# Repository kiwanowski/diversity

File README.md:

# diversity
an affordable DIY and open source alternative to the M8 tracker

## Limitations
The official firmware needs to be patched to work with this device.

## Support

[Please support the original M8 tracker author](https://www.patreon.com/trash80)

I won't provide support for any boards or schematics other than the ones provided in the repository.

I do not take reponsibility for any damage done. Please be sure that you understand what you are doing.

Creative Commons cc-by-sa 4.0 license.

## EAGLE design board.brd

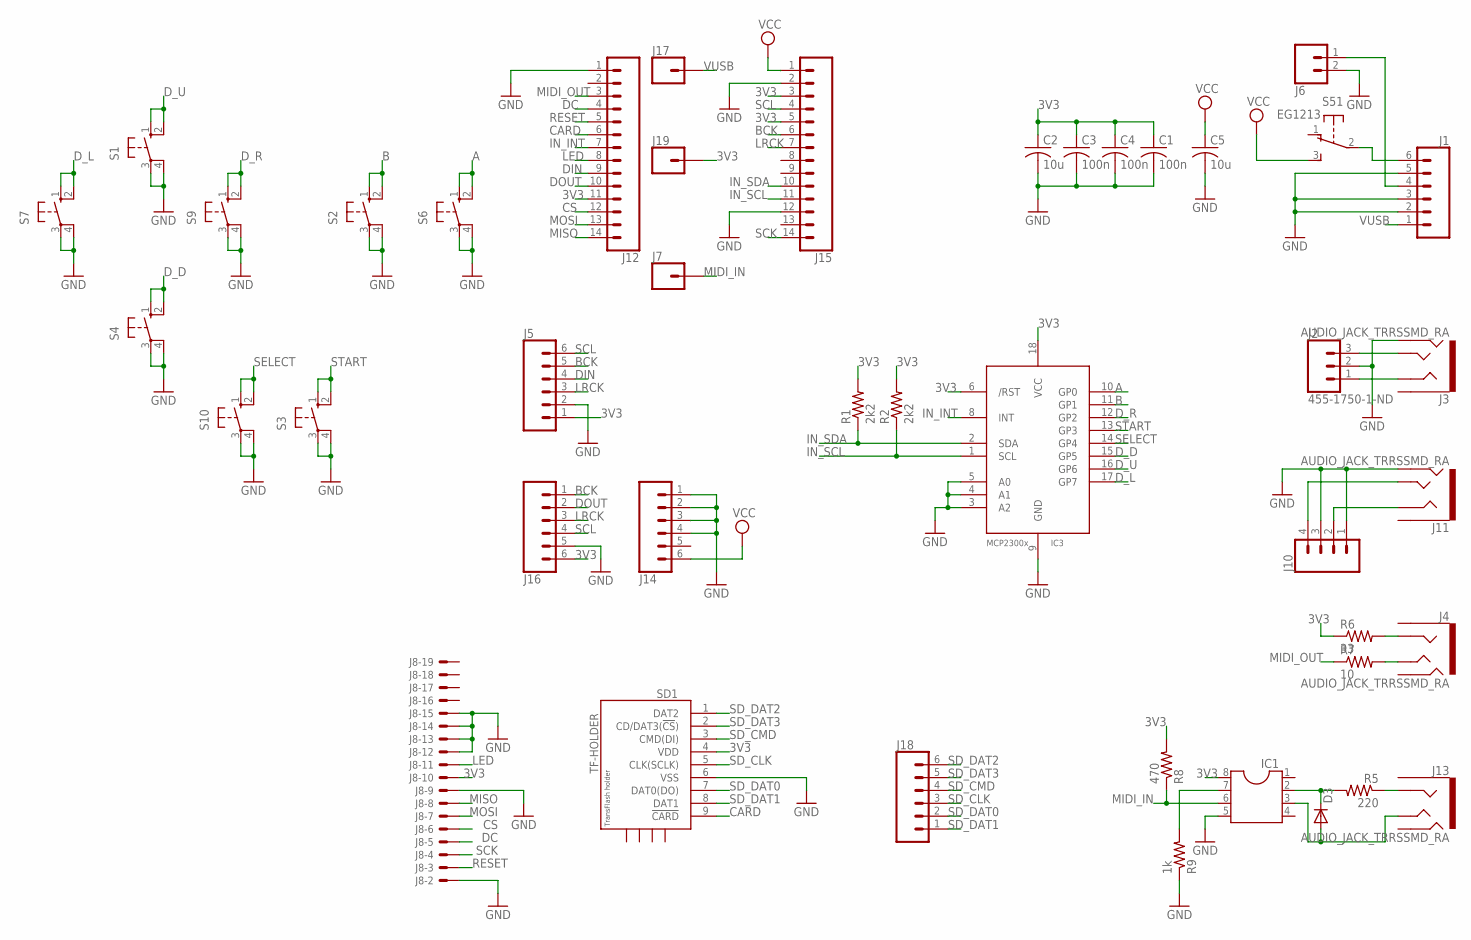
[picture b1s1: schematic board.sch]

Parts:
C1, C3, C4: 100n; C0805
C2, C5: 10u; C0805
D3: DIODE-MINIMELF; MINIMELF
IC1: DIL8; DIL08
IC3: MCP23008/SO; SO18W
J1, J5, J14, J16, J18: CONN_06SILK_FEMALE_PTH; 1X06
J2: 455-1750-1-ND; 1X03
J3, J4, J11, J13: AUDIO_JACK_TRRSSMD_RA; AUDIO_JACK_3.5MM_TRRS_SMD_RA
J6: CONN_02; 1X02
J7, J17, J19: CONN_01; 1X01
J8: XF2E-2015-1
J10: CONN_04; 1X04
J12, J15: CONN_14; 1X14
R1, R2: 2k2; R0805
R5: 220; R0805
R6: 33; R0805
R7: 10; R0805
R8: 470; R0805
R9: 1k; R0805
S1, S2, S3, S4, S6, S7, S9, S10: 10-XX; B3F-10XX
S5: EG1213
SD1: TF-HOLDER; TF-PULL

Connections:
3V3: C1.1, C2.1, C3.1, C4.1, IC1.8, IC3.6 (/RST), IC3.18 (VCC), J5.1, J8.10, J12.11, J15.3, J15.5, J16.6, J19.1, R1.2, R2.2, R6.1, R8.2, SD1.4 (VDD)
A: IC3.10 (GP0), S6.1 (S), S6.2 (S1)
B: IC3.11 (GP1), S2.1 (S), S2.2 (S1)
BCK: J5.5, J15.6, J16.1
CARD: J12.6, SD1.9 (!CARD)
CS: J8.6, J12.12
DC: J8.5, J12.4
DIN: J5.4, J12.9
DOUT: J12.10, J16.2
D_D: IC3.15 (GP5), S4.1 (S), S4.2 (S1)
D_L: IC3.17 (GP7), S7.1 (S), S7.2 (S1)
D_R: IC3.12 (GP2), S9.1 (S), S9.2 (S1)
D_U: IC3.16 (GP6), S1.1 (S), S1.2 (S1)
GND: C1.2, C2.2, C3.2, C4.2, C5.2, IC1.5, IC3.3 (A2), IC3.4 (A1), IC3.5 (A0), IC3.9 (GND), J1.2, J1.3, J1.5, J2.2, J3.RING2, J5.2, J6.2, J8.2, J8.9, J8.12, J8.13, J8.14, J8.15, J10.1, J10.3, J11.RING2, J12.1, J14.1, J14.2, J14.3, J14.4, J15.2, J15.12, J16.5, R9.1, S1.3, S1.4 (P1), S2.3, S2.4 (P1), S3.3, S3.4 (P1), S4.3, S4.4 (P1), S6.3, S6.4 (P1), S7.3, S7.4 (P1), S9.3, S9.4 (P1), S10.3, S10.4 (P1), SD1.6 (VSS)
IN_INT: IC3.8 (INT), J12.7
IN_SCL: IC3.1 (SCL), J15.11, R2.1
IN_SDA: IC3.2 (SDA), J15.10, R1.1
LED: J8.11, J12.8
LRCK: J5.3, J15.7, J16.3
MIDI_IN: IC1.6, J7.1, R8.1
MIDI_OUT: J12.3, R7.1
MISO: J8.8, J12.14
MOSI: J8.7, J12.13
unnamed: J2.3, J3.TIP
unnamed: J2.1, J3.RING1
unnamed: J10.4, J11.TIP
unnamed: J10.2, J11.RING1
unnamed: J1.4, J6.1
unnamed: J4.RING1, R6.2
unnamed: J4.TIP, R7.2
unnamed: J13.RING1, R5.1
unnamed: D3.C, IC1.2, R5.2
unnamed: D3.A, IC1.3, J13.TIP
unnamed: IC1.7, R9.2
unnamed: J1.6, S5.2
RESET: J8.3, J12.5
SCK: J8.4, J15.14
SCL: J5.6, J15.4, J16.4
SD_CLK: J18.3, SD1.5 (CLK(SCLK))
SD_CMD: J18.4, SD1.3 (CMD(DI))
SD_DAT0: J18.2, SD1.7 (DAT0(DO))
SD_DAT1: J18.1, SD1.8 (DAT1)
SD_DAT2: J18.6, SD1.1 (DAT2)
SD_DAT3: J18.5, SD1.2 (CD/DAT3(!CS!))
SELECT: IC3.14 (GP4), S10.1 (S), S10.2 (S1)
START: IC3.13 (GP3), S3.1 (S), S3.2 (S1)
VCC: C5.1, J14.6, J15.1, S5.3 (S)
VUSB: J1.1, J17.1

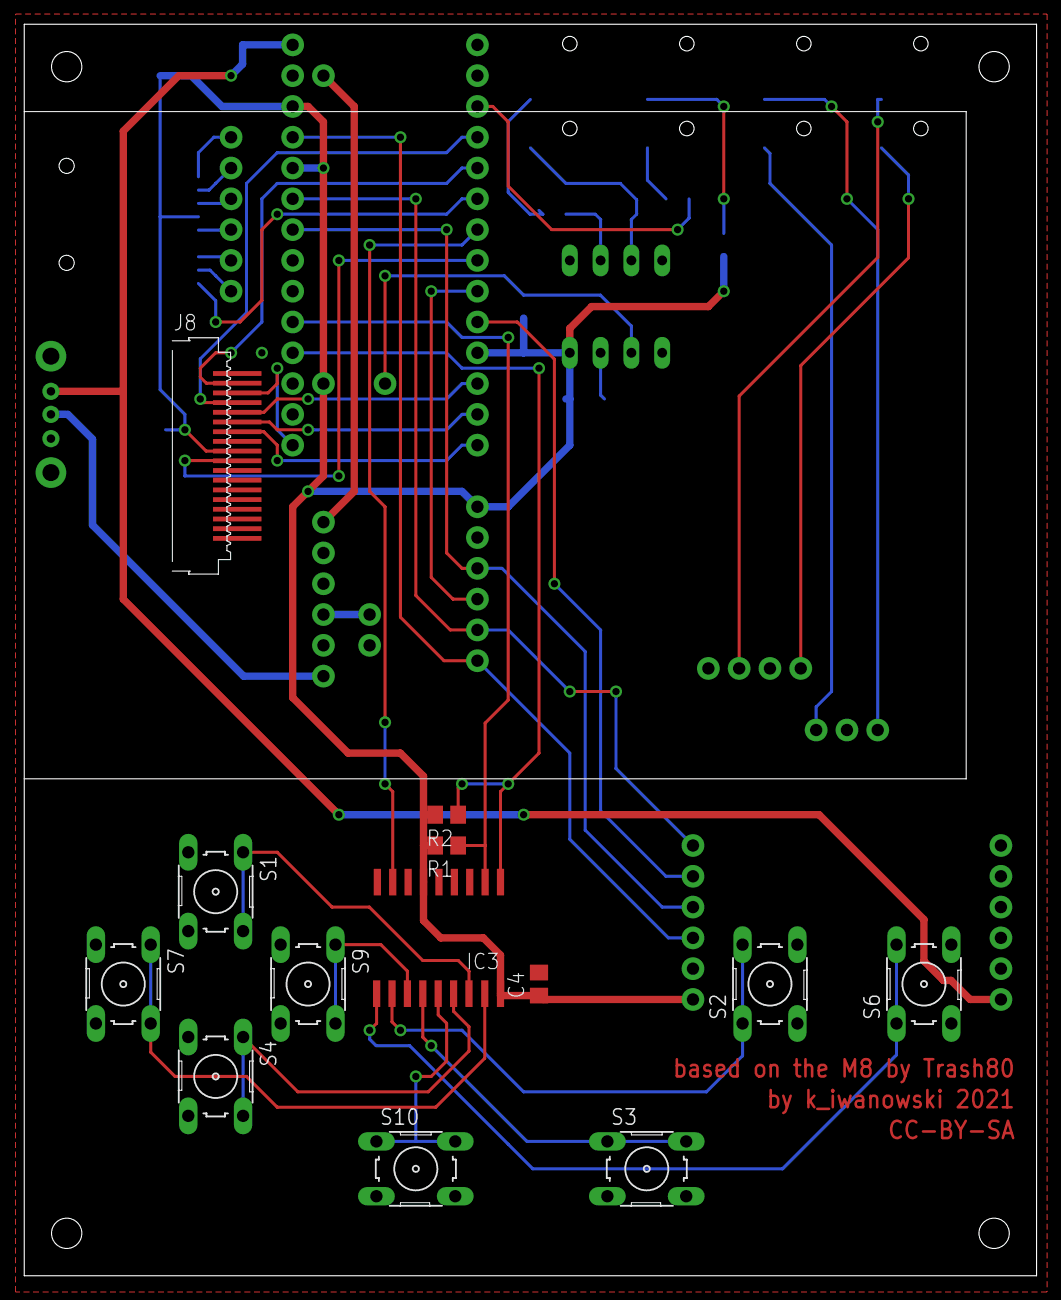
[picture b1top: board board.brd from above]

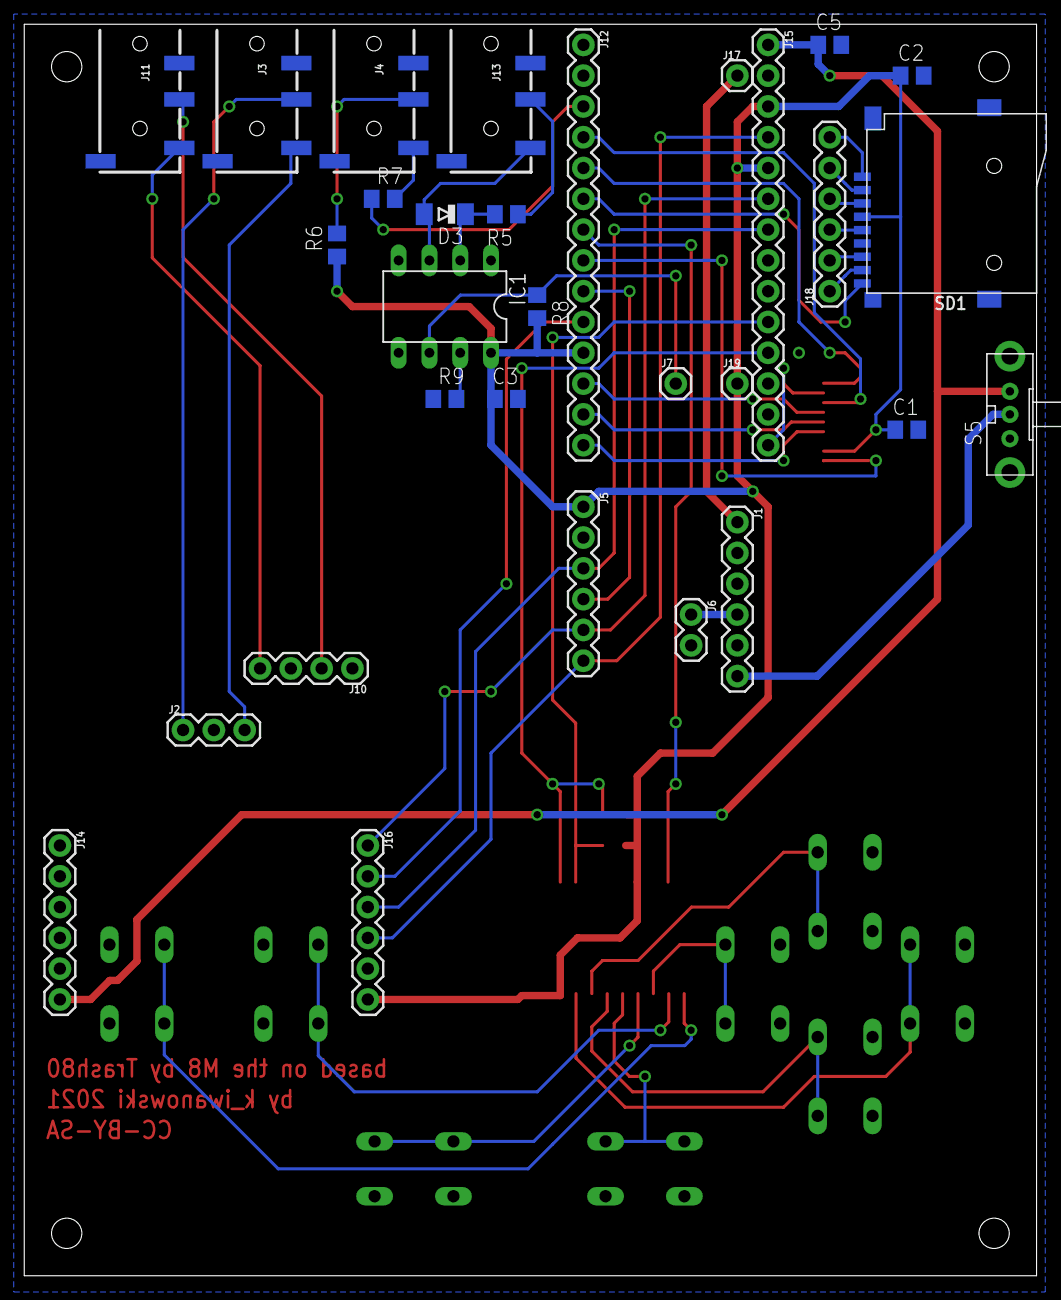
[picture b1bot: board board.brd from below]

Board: 2 copper layers, 83.5 x 103.2 mm, 43 parts (30 on the bottom side), 48 nets.

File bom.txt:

M8 board:

Teensy 4.0
S1, S2, S3, S4, S6, S7, S9, S10 - tact switch 6x6x8mm THT https://www.aliexpress.com/item/32872707582.html
S1, S2, S3, S4, S6, S7, S9, S10 - tact switch caps https://www.aliexpress.com/item/32888964798.html
J8 - 3.2 inch ILI9341 LCD without touch https://www.aliexpress.com/item/32861524235.html
J1 - MH CD42 battery charger module https://www.aliexpress.com/item/1005005185685973.html
PCM5102A DAC module https://www.aliexpress.com/item/4000397296348.html
PCM1808 ADC module https://www.aliexpress.com/item/32777376004.html
J9 - micro SD socket https://www.aliexpress.com/item/1005006288088367.html
IC3 - MCP23008-E/SO
S5 - slide switch https://www.aliexpress.com/item/32762926481.html
IC1 - 6N138
J3, J4, J11, J13 - headphone jack https://www.aliexpress.com/item/32439357849.html
J6 - 504050 1500mah battery

R1, R2 2k2 ohm 0805
R5 220 ohm 0805
R6 33 ohm 0805
R7 10 ohm 0805
R8 470 ohm 0805
R9 1k ohm 0805
C1, C2 10uF 0805
C3, C4 100nF 0805
D3 1N4148 SMD


Case:

4x Spacer M2.5 4mm https://www.aliexpress.com/item/1005007160597848.html
4x Spacer M2.5 8mm https://www.aliexpress.com/item/1005007160597848.html
4x Screw M2.5 5mm https://www.aliexpress.com/item/32961311508.html
4x Screw M2.5 12mm https://www.aliexpress.com/item/32961311508.html


SD adapter board:

R1 33 ohm 0805


PCM1808 ADC module modification:

5x 10uF 1206

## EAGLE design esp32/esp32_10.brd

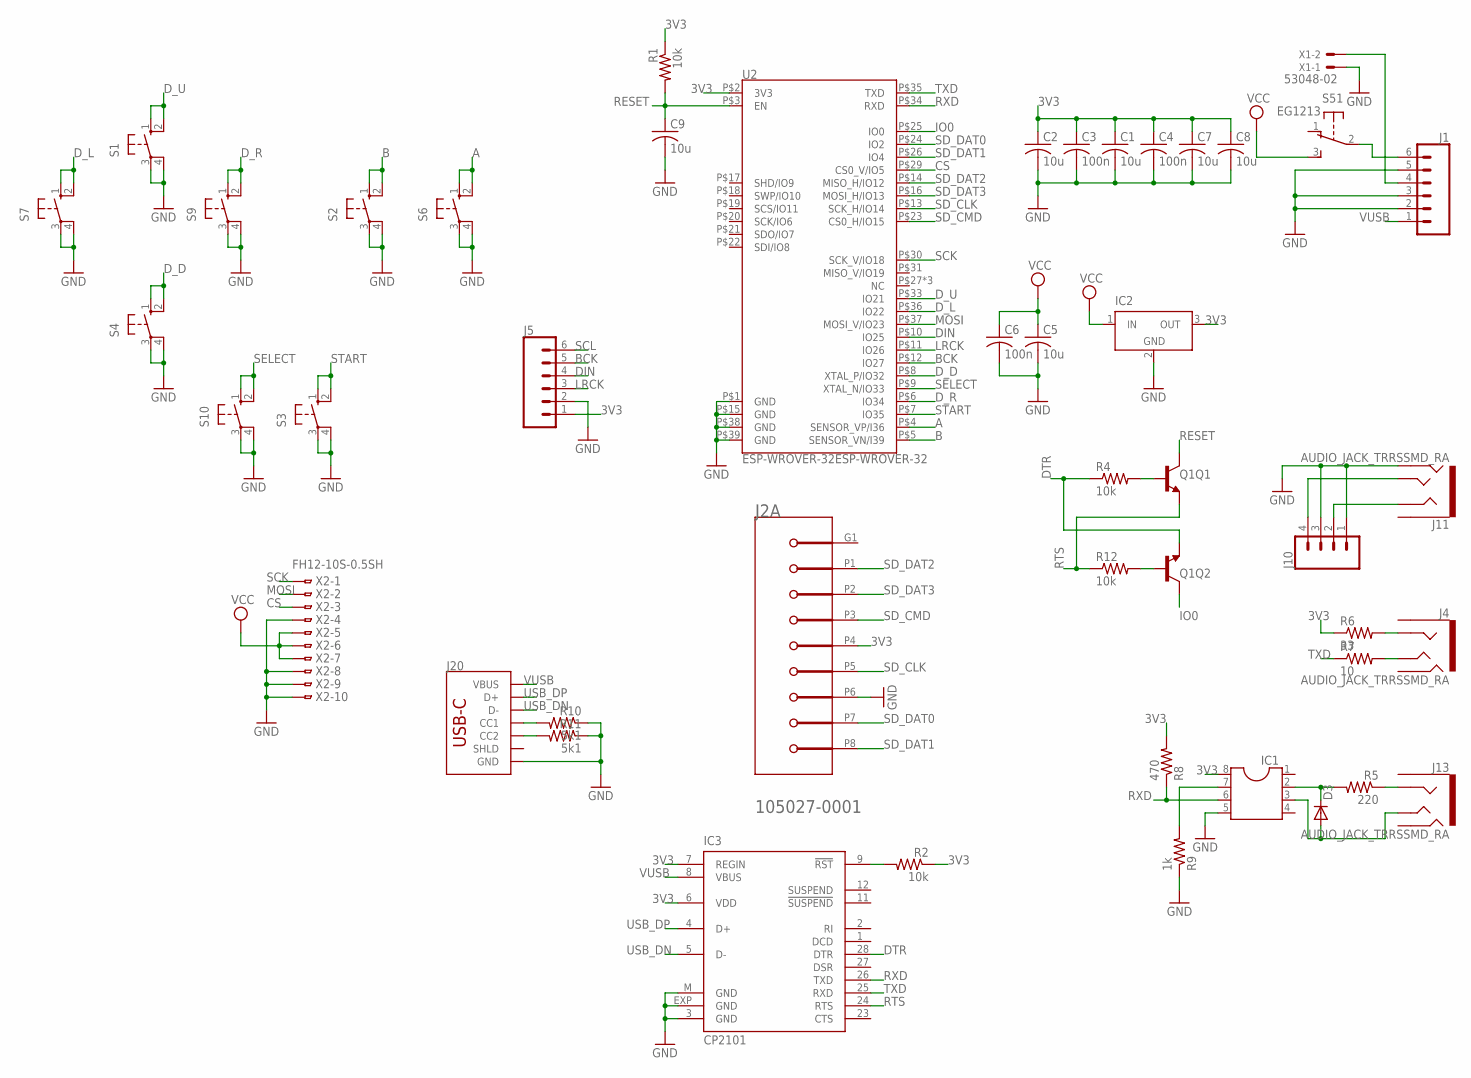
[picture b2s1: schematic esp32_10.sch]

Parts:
C1, C2, C5, C7, C8, C9: 10u; C0805
C3, C4, C6: 100n; C0805
D3: DIODE-MINIMELF; MINIMELF
IC1: DIL8; DIL08
IC2: LT1129CST5; SOT223
IC3: CP2101; MLP28
J1, J5: CONN_06SILK_FEMALE_PTH; 1X06
J2: MOLEX_INC_105027-0001MOLEX_INC_105027-0001_0_0; MOLEX_INC_105027-0001_0
J4, J11, J13: AUDIO_JACK_TRRSSMD_RA; AUDIO_JACK_3.5MM_TRRS_SMD_RA
J10: CONN_04; 1X04
J20: USB_C_2-LAYER_PADS; USB-C-16P-2LAYER-PADS
Q1: TRANS_NPN_DUAL-MBT3904DW1T1; SC70-6
R1, R2, R4, R12: 10k; R0805
R5: 220; R0805
R6: 33; R0805
R7: 10; R0805
R8: 470; R0805
R9: 1k; R0805
R10, R11: 5k1; R0805
S1, S2, S3, S4, S6, S7, S9, S10: 10-XX; B3F-10XX
S5: EG1213
U2: ESP-WROVER-32ESP-WROVER-32; ESP-WROVER-32
X1: 53048-02
X2: FH12-10S-0.5SH

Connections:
3V3: C1.1, C2.1, C3.1, C4.1, C7.1, C8.1, IC1.8, IC2.3 (OUT), IC3.6 (VDD), IC3.7 (REGIN), J2.P4 (VDD), J5.1, R1.1, R2.1, R6.1, R8.2, U2.P$2 (3V3)
A: S6.1 (S), S6.2 (S1), U2.P$4 (SENSOR_VP/I36)
B: S2.1 (S), S2.2 (S1), U2.P$5 (SENSOR_VN/I39)
BCK: J5.5, U2.P$12 (IO27)
CS: U2.P$29 (CS0_V/IO5), X2.3
DIN: J5.4, U2.P$10 (IO25)
DTR: IC3.28 (DTR), Q1.1 (E), R4.1
D_D: S4.1 (S), S4.2 (S1), U2.P$8 (XTAL_P/IO32)
D_L: S7.1 (S), S7.2 (S1), U2.P$36 (IO22)
D_R: S9.1 (S), S9.2 (S1), U2.P$6 (IO34)
D_U: S1.1 (S), S1.2 (S1), U2.P$33 (IO21)
GND: C1.2, C2.2, C3.2, C4.2, C5.2, C6.2, C7.2, C8.2, C9.2, IC1.5, IC2.2 (GND), IC2.4 (GND), IC3.3 (GND), IC3.EXP (GND), IC3.M (GND), J1.2, J1.3, J1.5, J2.P6 (VSS), J5.2, J10.1, J10.3, J11.RING2, J20.GND, J20.GND2 (GND), R9.1, R10.1, R11.1, S1.3, S1.4 (P1), S2.3, S2.4 (P1), S3.3, S3.4 (P1), S4.3, S4.4 (P1), S6.3, S6.4 (P1), S7.3, S7.4 (P1), S9.3, S9.4 (P1), S10.3, S10.4 (P1), U2.P$1 (GND), U2.P$15 (GND), U2.P$38 (GND), U2.P$39 (GND), X1.1, X2.4, X2.8, X2.9, X2.10
IO0: Q1.6 (C), U2.P$25 (IO0)
LRCK: J5.3, U2.P$11 (IO26)
MOSI: U2.P$37 (MOSI_V/IO23), X2.2
unnamed: J10.4, J11.TIP
unnamed: J10.2, J11.RING1
unnamed: J1.4, X1.2
unnamed: Q1.2 (B), R12.2
unnamed: J20.A5 (CC1), R10.2
unnamed: J20.B5 (CC2), R11.2
unnamed: Q1.5 (B), R4.2
unnamed: J4.RING1, R6.2
unnamed: J4.TIP, R7.2
unnamed: J13.RING1, R5.1
unnamed: D3.C, IC1.2, R5.2
unnamed: D3.A, IC1.3, J13.TIP
unnamed: IC1.7, R9.2
unnamed: J1.6, S5.2
unnamed: IC3.9 (!RST), R2.2
RESET: C9.1, Q1.3 (C), R1.2, U2.P$3 (EN)
RTS: IC3.24 (RTS), Q1.4 (E), R12.1
RXD: IC1.6, IC3.26 (TXD), R8.1, U2.P$34 (RXD)
SCK: U2.P$30 (SCK_V/IO18), X2.1
SCL: J5.6
SD_CLK: J2.P5 (CLK), U2.P$13 (SCK_H/IO14)
SD_CMD: J2.P3 (CMD), U2.P$23 (CS0_H/IO15)
SD_DAT0: J2.P7 (DAT0), U2.P$24 (IO2)
SD_DAT1: J2.P8 (DAT1), U2.P$26 (IO4)
SD_DAT2: J2.P1 (DAT2), U2.P$14 (MISO_H/IO12)
SD_DAT3: J2.P2 (CD/DAT3), U2.P$16 (MOSI_H/IO13)
SELECT: S10.1 (S), S10.2 (S1), U2.P$9 (XTAL_N/IO33)
START: S3.1 (S), S3.2 (S1), U2.P$7 (IO35)
TXD: IC3.25 (RXD), R7.1, U2.P$35 (TXD)
USB_DN: IC3.5 (D-), J20.A7 (D-), J20.B7 (D-)
USB_DP: IC3.4 (D+), J20.A6 (D+), J20.B6 (D+)
VCC: C5.1, C6.1, IC2.1 (IN), S5.3 (S), X2.5, X2.6, X2.7
VUSB: IC3.8 (VBUS), J1.1, J20.VBUS1 (VBUS), J20.VBUS2 (VBUS)

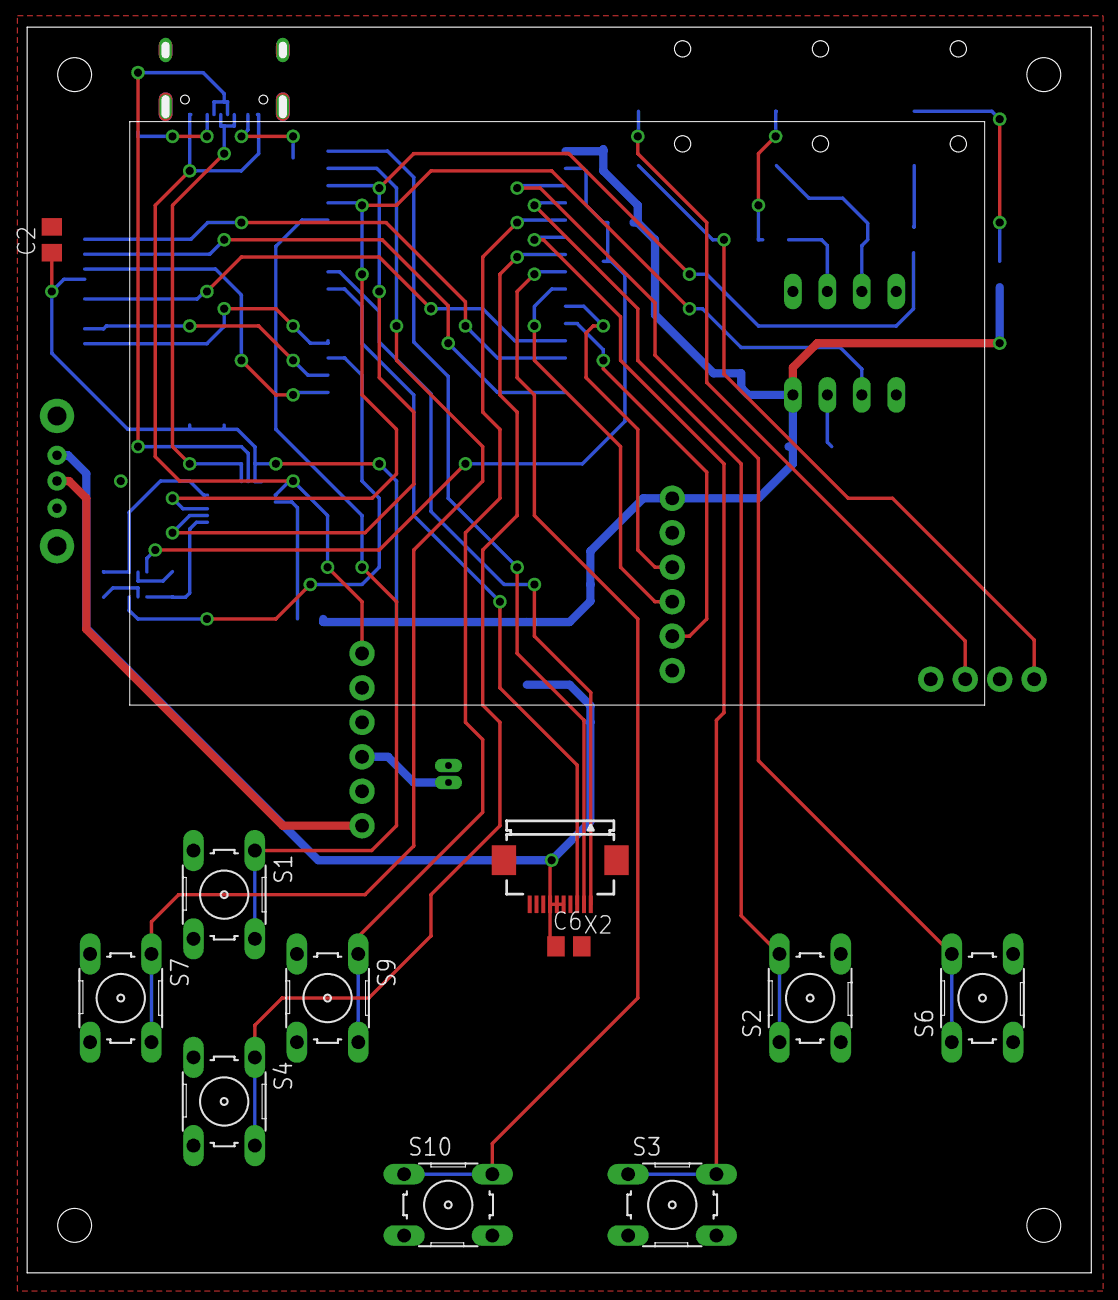
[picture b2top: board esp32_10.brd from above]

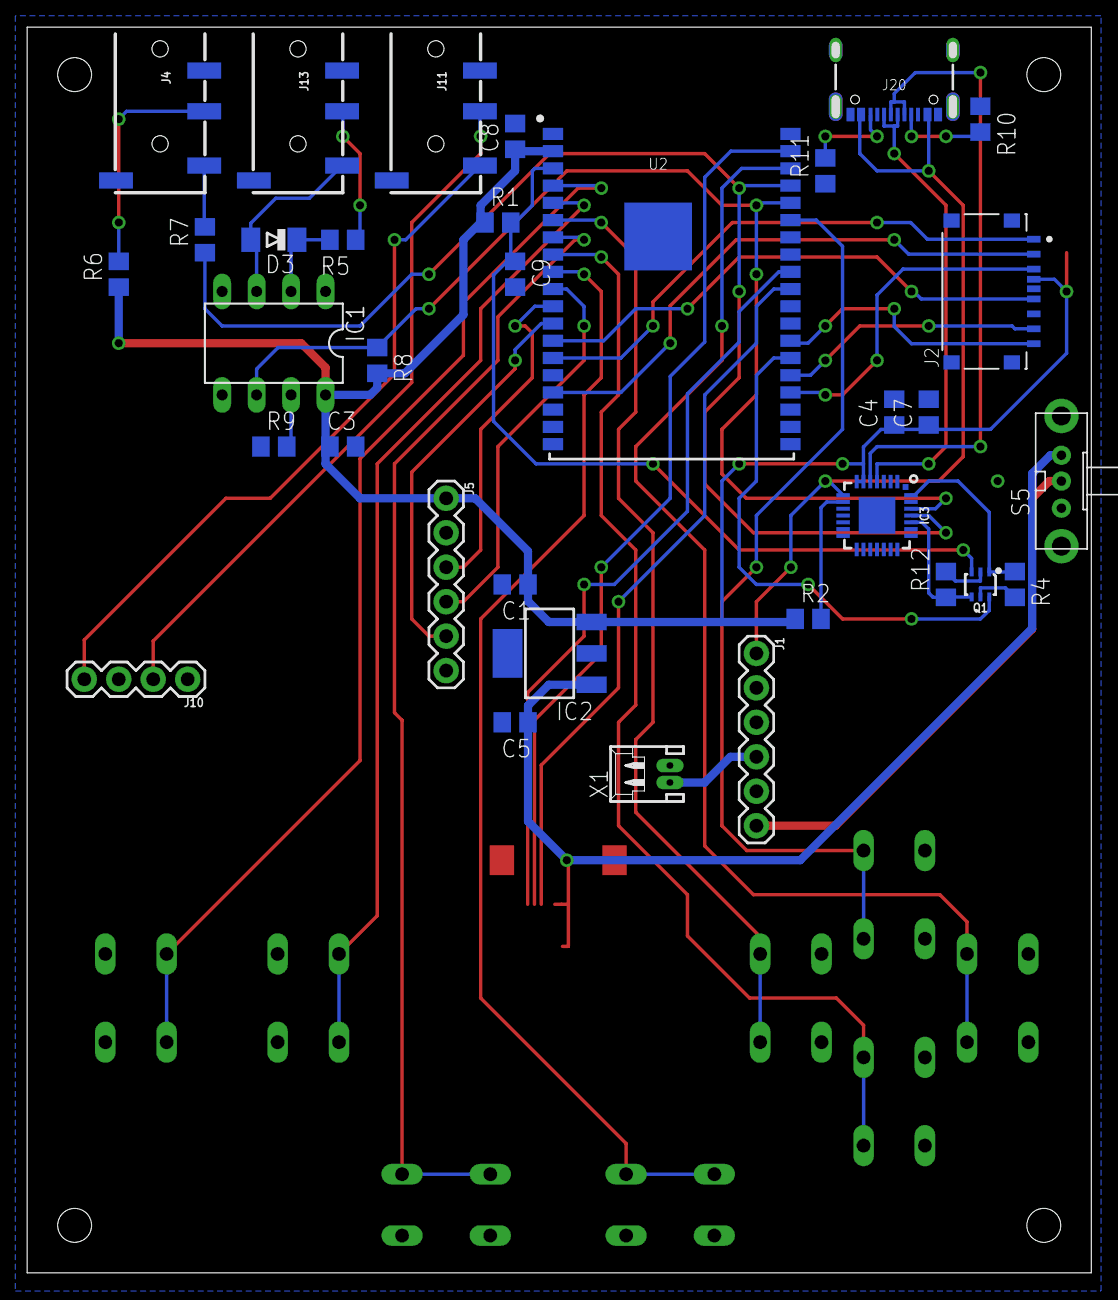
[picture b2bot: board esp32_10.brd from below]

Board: 2 copper layers, 77.8 x 91.2 mm, 45 parts (34 on the bottom side), 47 nets.

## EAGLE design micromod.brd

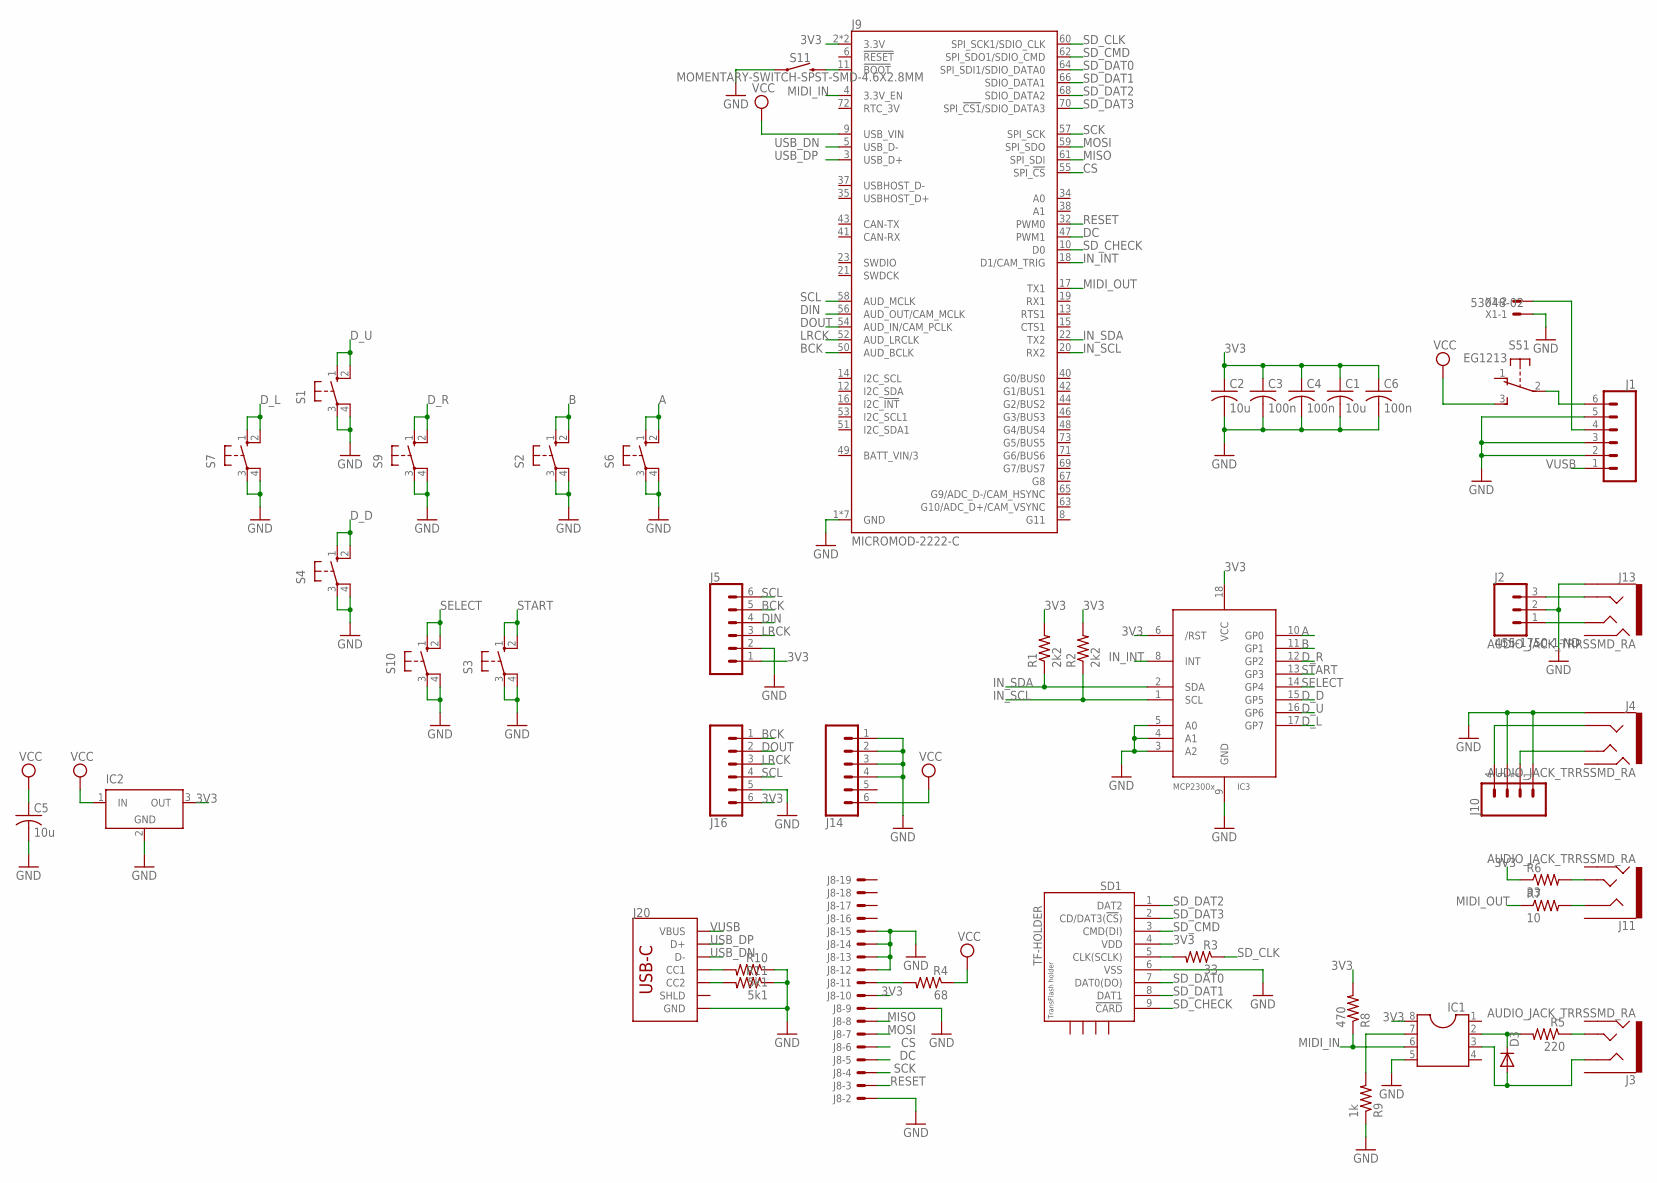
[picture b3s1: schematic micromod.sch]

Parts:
C1, C2, C5: 10u; C0805
C3, C4, C6: 100n; C0805
D3: DIODE-MINIMELF; MINIMELF
IC1: DIL8; DIL08
IC2: LT1129CST5; SOT223
IC3: MCP23008/SO; SO18W
J1, J5, J14, J16: CONN_06SILK_FEMALE_PTH; 1X06
J2: 455-1750-1-ND; 1X03
J3, J4, J11, J13: AUDIO_JACK_TRRSSMD_RA; AUDIO_JACK_3.5MM_TRRS_SMD_RA
J8: XF2E-2015-1
J9: MICROMOD-2222-C; M.2-CONNECTOR-E
J10: CONN_04; 1X04
J20: USB_C_2-LAYER_PADS; USB-C-16P-2LAYER-PADS
R1, R2: 2k2; R0805
R3, R6: 33; R0805
R4: 68; R0805
R5: 220; R0805
R7: 10; R0805
R8: 470; R0805
R9: 1k; R0805
R10, R11: 5k1; R0805
S1, S2, S3, S4, S6, S7, S9, S10: 10-XX; B3F-10XX
S5: EG1213
S11: MOMENTARY-SWITCH-SPST-SMD-4.6X2.8MM; TACTILE_SWITCH_SMD_4.6X2.8MM
SD1: TF-HOLDER; TF-PULL
X1: 53048-02

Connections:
3V3: C1.1, C2.1, C3.1, C4.1, C6.1, IC1.8, IC2.3 (OUT), IC3.6 (/RST), IC3.18 (VCC), J5.1, J8.10, J9.2 (3.3V), J9.74 (3.3V), J16.6, R1.2, R2.2, R6.1, R8.2, SD1.4 (VDD)
A: IC3.10 (GP0), S6.1 (S), S6.2 (S1)
B: IC3.11 (GP1), S2.1 (S), S2.2 (S1)
BCK: J5.5, J9.50 (AUD_BCLK), J16.1
CS: J8.6, J9.55 (SPI_!CS!)
DC: J8.5, J9.47 (PWM1)
DIN: J5.4, J9.56 (AUD_OUT/CAM_MCLK)
DOUT: J9.54 (AUD_IN/CAM_PCLK), J16.2
D_D: IC3.15 (GP5), S4.1 (S), S4.2 (S1)
D_L: IC3.17 (GP7), S7.1 (S), S7.2 (S1)
D_R: IC3.12 (GP2), S9.1 (S), S9.2 (S1)
D_U: IC3.16 (GP6), S1.1 (S), S1.2 (S1)
GND: C1.2, C2.2, C3.2, C4.2, C5.2, C6.2, IC1.5, IC2.2 (GND), IC2.4 (GND), IC3.3 (A2), IC3.4 (A1), IC3.5 (A0), IC3.9 (GND), J1.2, J1.3, J1.5, J2.2, J4.EARTH, J5.2, J8.2, J8.9, J8.12, J8.13, J8.14, J8.15, J9.1 (GND), J9.7 (GND), J9.33 (GND), J9.36 (GND), J9.39 (GND), J9.45 (GND), J9.75 (GND), J10.1, J10.3, J13.EARTH, J14.1, J14.2, J14.3, J14.4, J16.5, J20.GND, J20.GND2 (GND), R9.1, R10.1, R11.1, S1.3, S1.4 (P1), S2.3, S2.4 (P1), S3.3, S3.4 (P1), S4.3, S4.4 (P1), S6.3, S6.4 (P1), S7.3, S7.4 (P1), S9.3, S9.4 (P1), S10.3, S10.4 (P1), S11.1, S11.2 (1), SD1.6 (VSS), X1.1
IN_INT: IC3.8 (INT), J9.18 (D1/CAM_TRIG)
IN_SCL: IC3.1 (SCL), J9.20 (RX2), R2.1
IN_SDA: IC3.2 (SDA), J9.22 (TX2), R1.1
LRCK: J5.3, J9.52 (AUD_LRCLK), J16.3
MIDI_IN: IC1.6, J9.4 (3.3V_EN), R8.1
MIDI_OUT: J9.17 (TX1), R7.1
MISO: J8.8, J9.61 (SPI_SDI)
MOSI: J8.7, J9.59 (SPI_SDO)
unnamed: J8.11, R4.2
unnamed: J2.3, J13.RING1
unnamed: J2.1, J13.TIP
unnamed: J4.RING1, J10.4
unnamed: J4.TIP, J10.2
unnamed: J1.4, X1.2
unnamed: R3.2, SD1.5 (CLK(SCLK))
unnamed: J20.A5 (CC1), R10.2
unnamed: J20.B5 (CC2), R11.2
unnamed: J9.11 (!BOOT!), S11.3 (2), S11.4 (2)
unnamed: J3.TIP, R5.1
unnamed: J11.TIP, R6.2
unnamed: J11.RING1, R7.2
unnamed: D3.C, IC1.2, R5.2
unnamed: D3.A, IC1.3, J3.RING1
unnamed: IC1.7, R9.2
unnamed: J1.6, S5.2
RESET: J8.3, J9.32 (PWM0)
SCK: J8.4, J9.57 (SPI_SCK)
SCL: J5.6, J9.58 (AUD_MCLK), J16.4
SD_CHECK: J9.10 (D0), SD1.9 (!CARD)
SD_CLK: J9.60 (SPI_SCK1/SDIO_CLK), R3.1
SD_CMD: J9.62 (SPI_SDO1/SDIO_CMD), SD1.3 (CMD(DI))
SD_DAT0: J9.64 (SPI_SDI1/SDIO_DATA0), SD1.7 (DAT0(DO))
SD_DAT1: J9.66 (SDIO_DATA1), SD1.8 (DAT1)
SD_DAT2: J9.68 (SDIO_DATA2), SD1.1 (DAT2)
SD_DAT3: J9.70 (SPI_!CS1!/SDIO_DATA3), SD1.2 (CD/DAT3(!CS!))
SELECT: IC3.14 (GP4), S10.1 (S), S10.2 (S1)
START: IC3.13 (GP3), S3.1 (S), S3.2 (S1)
USB_DN: J9.5 (USB_D-), J20.A7 (D-), J20.B7 (D-)
USB_DP: J9.3 (USB_D+), J20.A6 (D+), J20.B6 (D+)
VCC: C5.1, IC2.1 (IN), J9.9 (USB_VIN), J14.6, R4.1, S5.3 (S)
VUSB: J1.1, J20.VBUS1 (VBUS), J20.VBUS2 (VBUS)

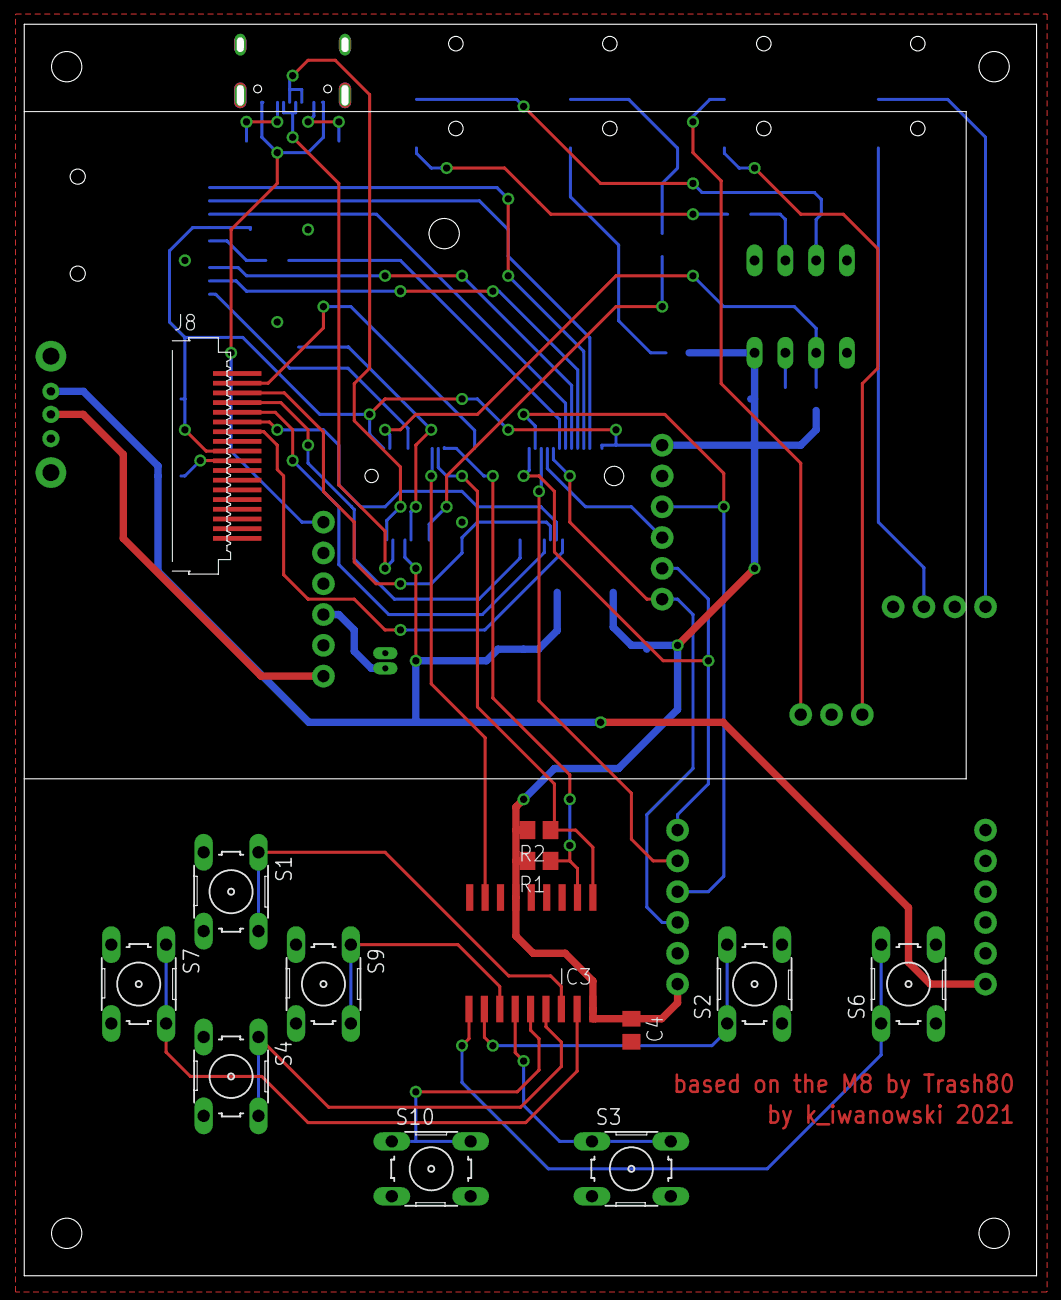
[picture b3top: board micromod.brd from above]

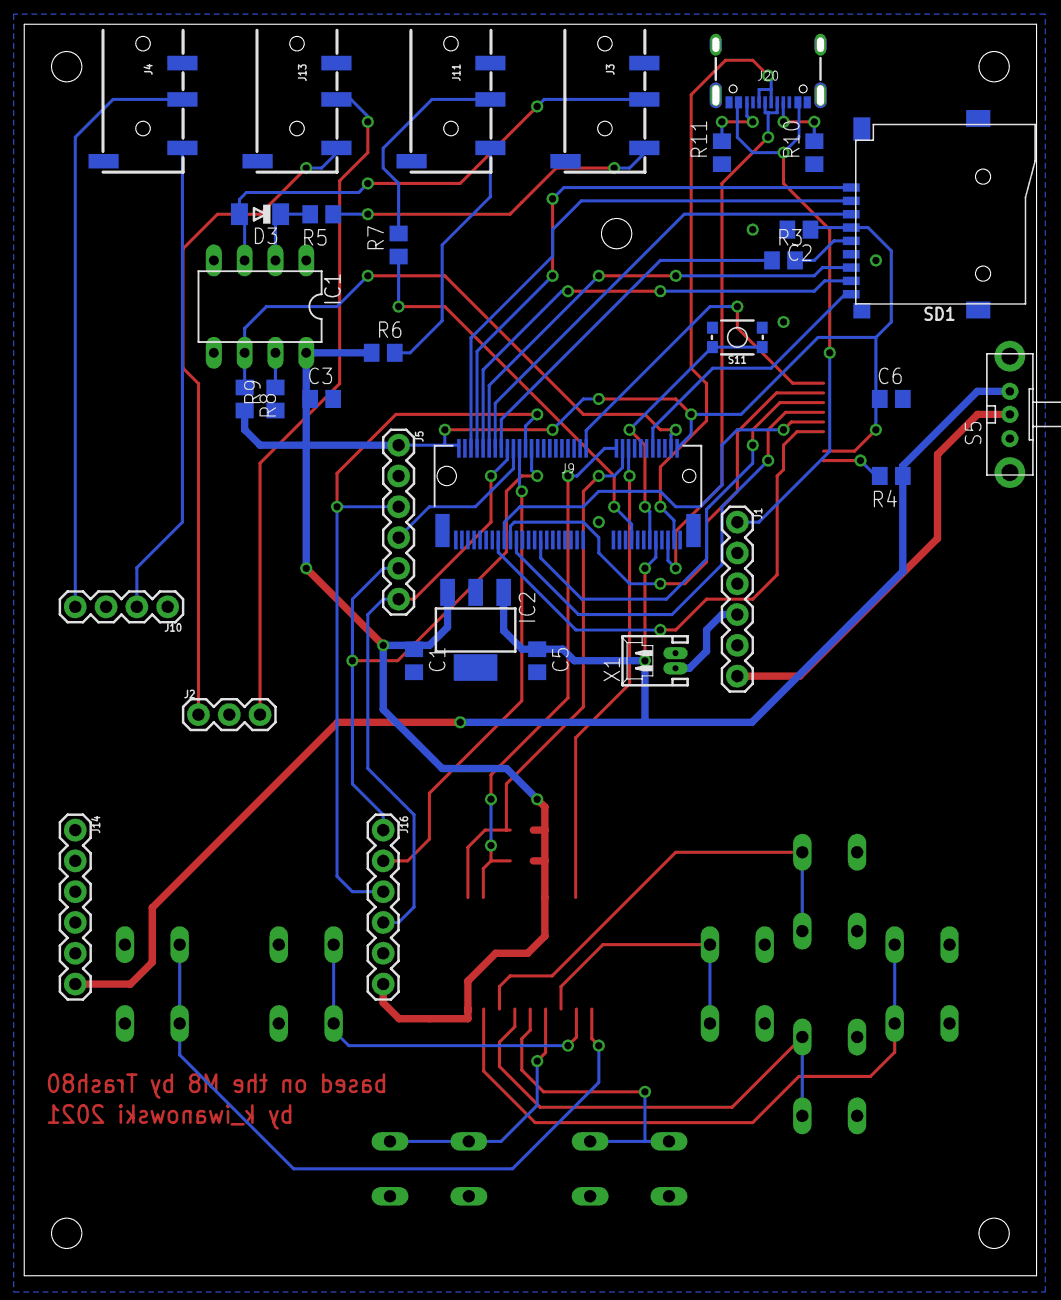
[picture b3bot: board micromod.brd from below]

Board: 2 copper layers, 82.9 x 102.6 mm, 46 parts (33 on the bottom side), 54 nets.

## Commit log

2021-12-17 readme update
2022-07-12 micromod version
2022-07-15 adapter fix
2023-04-11 Update README.md
    Added mention of micromod version being proof of concept
2023-06-26 tests for micromod
    added test programs for the micromod pcb
2024-01-21 esp32 handheld
2024-04-28 changed serial port
2024-08-24 pcb fixes
    -added an option for the LCD backlight to be adjusted in the device menu
    -changed the sd card slot, now its possible to run the device without an sd card
    -changed the case filename - the case probably has to be updated due to the new sd card slot
2024-08-24 small pcb fix
2024-09-30 deleted unusable boards
2024-10-26 added a firmware patch
2024-10-27 pcb update
2025-05-12 Removing outdated files
2025-07-15 Added the new BOM file

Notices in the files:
parts and their libraries:
lbr_SparkFun-Eagle-Libraries_SparkFun-Co: Licensing: Creative Commons ShareAlike 4.0 International - https://creativecommons.org/licenses/by-sa/4.0
